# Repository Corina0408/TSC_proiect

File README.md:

link diagrama bloc: https://files.fm/u/eejnjsv4u4 

link Bill of Materials: https://docs.google.com/spreadsheets/d/1bhhom45KiLlfx5yxiHwmtoe4DynNoX60qw5_dlvZoLE/edit?usp=sharing 

Descrierea functionalitatii: 

	dispozitiv smart, construit in jurul microcontrollerului ESP32-C6, care integreaza senzori de afisaj OLED, LED RGB pentru vizual, control tactil si un potentiometru.

	Module si componente utilizate

    ESP32-C6: microcontroller principal, care gestioneaza toate componentele, comunicarea si logica dispozitivului

    BME280: senzor de temperatura, umiditate si presiune

    Display OLED (SSD1306): afiseaza informatii de la senzori si statusul sistemului

    LED RGB WS2812B: ofera feedback vizual configurabil

    TTP223: buton tactil folosit pentru interactiuni simple, cum ar fi pornirea luminii sau schimbarea modului de afisare

    Potentiometru: permite reglarea unui parametru analogic

    Reed switch: senzor magnetic digital, detecteaza apropierea unui magnet

	Interfete si comunicatie

    I2C: folosita pentru a conecta atat senzorul BME280, cat si display-ul OLED pe acelasi bus. ESP32-C6 gestioneaza ambele componente fara conflicte.

    PWM/One-wire: pentru LED-ul WS2812B, controlat prin semnal digital specific.

    Digital input: pentru butonul capacitiv si reed switch.

    Analog input (ADC): pentru citirea potentiometrului.

Procesare si comportament

ESP32-C6 colecteaza datele de la senzori si le afiseaza pe ecran. In plus, permite interactiuni tactile si vizuale cu utilizatorul

Descrierea pinilor ESP32-C6:

BME280 (I2C)

    GPIO8 (SDA) – Bus I2C partajat cu display

    GPIO9 (SCL)

OLED SSD1306 (I2C)

    GPIO8 (SDA) – Partajare eficienta de pini

    GPIO9 (SCL)

WS2812B (PWM)

    GPIO7 – Output digital cu timing precis

TTP223 (Digital)

    GPIO6 – Pin liber, ideal pentru input

Potentiometru (Analog)

    GPIO4 (ADC1) – Suporta ADC, masoara tensiune

Reed switch (Digital)

    GPIO5 – Citire stare logica simpla

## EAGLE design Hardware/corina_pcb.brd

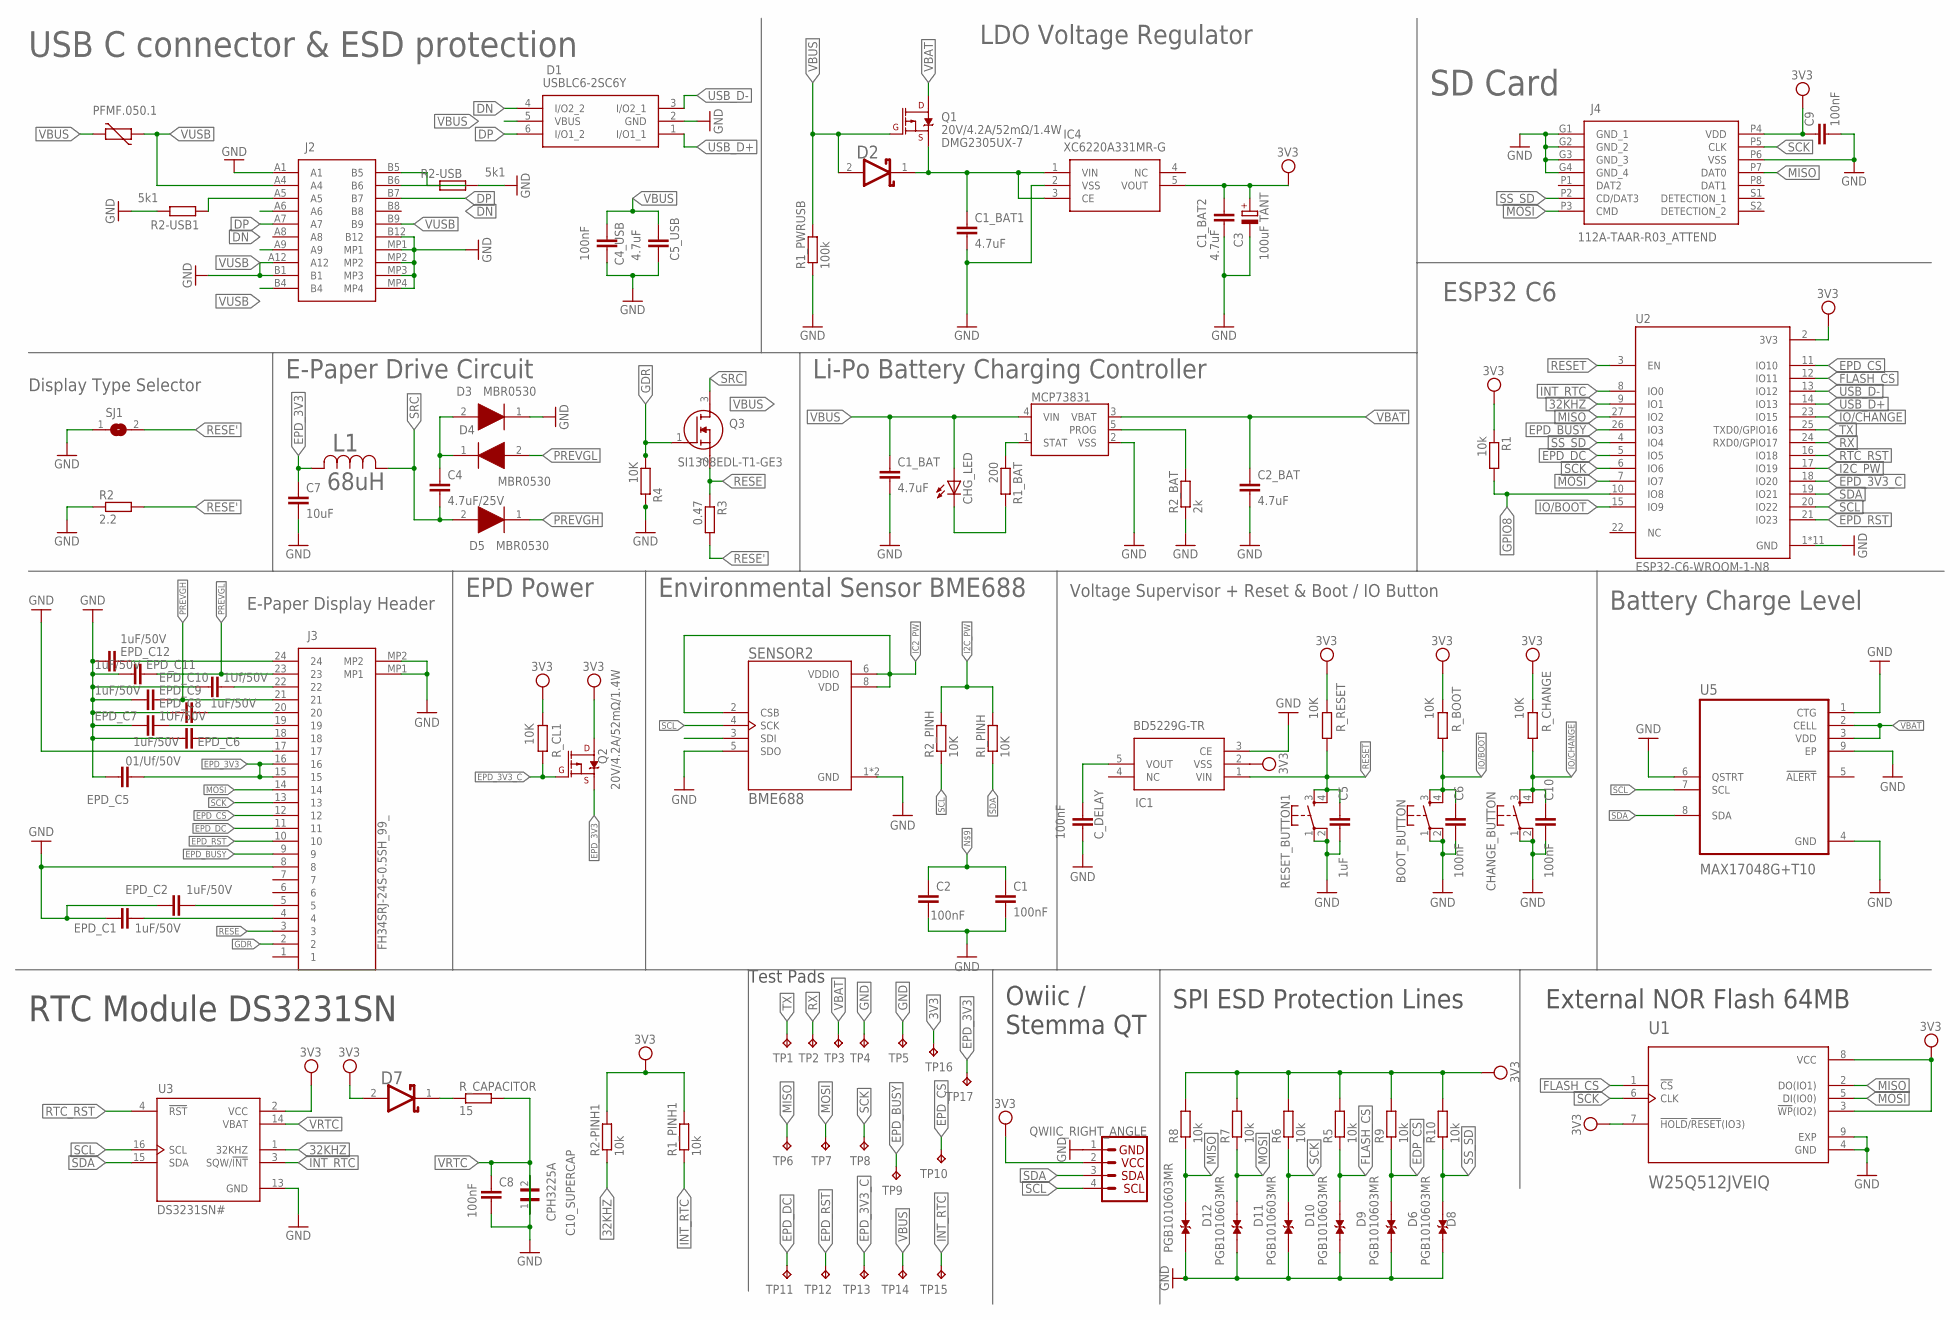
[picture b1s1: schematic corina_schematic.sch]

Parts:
BOOT_BUTTON: BUTTON_CUSYOMV1; MYBUTTON
C1, C2, C6, C8, C10: 100nF; ESP32_WROVER_EAGLE-LTSPICE_C0402
C1_BAT, C1_BAT2, C2_BAT: 4.7uF; ESP32_WROVER_EAGLE-LTSPICE_C0402
C1_BAT1, C5_USB: 4.7uF; EAGLE-LTSPICE_C0402
C3: 100uF TANT; RCL_CT3528
C4: 4.7uF/25V; ESP32_WROVER_EAGLE-LTSPICE_C0402
C4_USB, C9: 100nF; EAGLE-LTSPICE_C0402
C5: 1uF; ESP32_WROVER_EAGLE-LTSPICE_C0402
C7: 10uF; ESP32_WROVER_EAGLE-LTSPICE_C0402
C10_SUPERCAP: CPH3225A; CAPCP3225X100N
CHANGE_BUTTON: BUTTON_CUSYOMV1; MYBUTTON
CHG_LED: ADAFRUIT_LEDCHIP-LED0603; ADAFRUIT_CHIP-LED0603
C_DELAY: 100nF; ESP32_WROVER_EAGLE-LTSPICE_C0402
D1: USBLC6-2SC6Y; SOT95P280X145-6N
D2, D7: ESP32_WROVER_AVX---SD0805S020S1R0_AVX_SD0805S020S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; ESP32_WROVER_AVX---SD0805S020S1R0_AVX_SD0805S020S1R0_0
D3, D4, D5: MBR0530; SOD3716X135N
D6, D8, D9, D10, D11, D12: PGB1010603MR; DIOC1608X36N
EPD_C1, EPD_C2, EPD_C6, EPD_C8, EPD_C9, EPD_C11, EPD_C12: 1uF/50V; ESP32_WROVER_EAGLE-LTSPICE_C0402
EPD_C5: 01/Uf/50V; ESP32_WROVER_EAGLE-LTSPICE_C0402
EPD_C7: 1UF/50V; ESP32_WROVER_EAGLE-LTSPICE_C0402
EPD_C10: 1Uf/50V; ESP32_WROVER_EAGLE-LTSPICE_C0402
IC1: BD5229G-TR; SOT95P280X120-5N
IC4: XC6220A331MR-G; SOT95P280X120-5N
J1: QWIIC_RIGHT_ANGLE; JST04_1MM_RA
J2: SAMACSYS_PARTS_USB4110-GF-A; SAMACSYS_PARTS_USB4110GFA
J3: FH34SRJ-24S-0.5SH_99_; FH34SRJ24S05SH99
J4: 112A-TAAR-R03_ATTEND; 112ATAARR03ATTEND
L1: 68uH; IND_4828-WE-TPC_WRE
MCP73831: ESP32_WROVER_SPARKFUN-IC-POWER_MCP73831; ESP32_WROVER_SPARKFUN-IC-POWER_SOT23-5
PFMF.050.1: ESP32C6_VARISTORCN1812; ESP32C6_VARISTOR_CT/CN1812
Q1, Q2: 20V/4.2A/52mΩ/1.4W; ESP32_WROVER_SPARKFUN-DISCRETESEMI_SOT23-3
Q3: SI1308EDL-T1-GE3; SOT65P210X110-3N
R1, R1_PINH1, R2-PINH1, R5, R6, R7, R8, R9, R10: 10k; ESP32_WROVER_EAGLE-LTSPICE_R0402
R1_BAT: 200; ESP32_WROVER_EAGLE-LTSPICE_R0402
R1_PWRUSB: 100k; ESP32_WROVER_EAGLE-LTSPICE_R0402
R2: 2.2; ESP32_WROVER_EAGLE-LTSPICE_R0402
R2-USB, R2-USB1: 5k1; ESP32_WROVER_EAGLE-LTSPICE_R0402
R2_BAT: 2k; ESP32_WROVER_EAGLE-LTSPICE_R0402
R2_PINH, R4: 10K; ESP32_WROVER_EAGLE-LTSPICE_R0402
R3: 0.47; ESP32_WROVER_EAGLE-LTSPICE_R0402
RESET_BUTTON1: BUTTON_CUSYOMV1; MYBUTTON
RI_PINH: 10K; ESP32_WROVER_EAGLE-LTSPICE_R0402
R_BOOT: 10K; ESP32_WROVER_EAGLE-LTSPICE_R0402
R_CAPACITOR: 15; ESP32_WROVER_EAGLE-LTSPICE_R0402
R_CHANGE: 10K; ESP32_WROVER_EAGLE-LTSPICE_R0402
R_CL1: 10K; ESP32_WROVER_EAGLE-LTSPICE_R0402
R_RESET: 10K; ESP32_WROVER_EAGLE-LTSPICE_R0402
SENSOR2: BME688; ESP32_WROVER_BME680_PSON80P300X300X100-8N
SJ1: SJ
TP1, TP2, TP3, TP4, TP5, TP6, TP7, TP8, TP9, TP10, TP11, TP12, TP13, TP14, TP15, TP16, TP17: TPTP20R; TP20R
U1: W25Q512JVEIQ; SON127P600X800X80-9N
U2: ESP32-C6-WROOM-1-N8; XCVR_ESP32-C6-WROOM-1-N8
U3: DS3231SN#; SOIC127P1032X265-16N
U5: MAX17048G+T10; SON50P200X200X80-9N

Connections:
3V3: C1_BAT2.1, C3.+, C9.1, D7.2 (ANODE), IC1.2 (VSS), IC4.5 (VOUT), J1.2, J4.P4 (VDD), Q2.3 (D), R1.1, R1_PINH1.2, R2-PINH1.2, R5.2, R6.2, R7.2, R8.2, R9.2, R10.2, R_BOOT.2, R_CHANGE.2, R_CL1.2, R_RESET.2, TP16.TP, U1.3 (!WP!(IO2)), U1.7 (!HOLD!/!RESET!(IO3)), U1.8 (VCC), U2.2 (3V3), U3.2 (VCC)
32KHZ: R2-PINH1.1, U2.9 (IO1), U3.1 (32KHZ)
DN: J2.A7
DP: J2.A6
EDP_CS: D9.2, R9.1
EPD_3V3: C7.1, EPD_C5.2, J3.15, J3.16, L1.2, Q2.2 (S), TP17.TP
EPD_3V3_C: Q2.1 (G), R_CL1.1, TP13.TP, U2.18 (IO20)
EPD_BUSY: J3.9, TP9.TP, U2.26 (IO3)
EPD_CS: J3.12, TP10.TP, U2.11 (IO10)
EPD_DC: J3.11, TP11.TP, U2.5 (IO5)
EPD_RST: J3.10, TP12.TP, U2.21 (IO23)
FLASH_CS: D10.2, R5.1, U1.1 (!CS), U2.12 (IO11)
GDR: J3.2, Q3.1 (G), R4.2
GND: BOOT_BUTTON.1, BOOT_BUTTON.2, C1.2, C1_BAT.2, C1_BAT1.2, C1_BAT2.2, C2.2, C2_BAT.2, C3.-, C4_USB.2, C5.2, C5_USB.2, C6.2, C7.2, C8.2, C9.2, C10.2, C10_SUPERCAP.2, CHANGE_BUTTON.1, CHANGE_BUTTON.2, C_DELAY.2, D1.2 (GND), D3.1 (K), D6.1, D8.1, D9.1, D10.1, D11.1, D12.1, EPD_C1.1, EPD_C2.1, EPD_C5.1, EPD_C6.2, EPD_C7.2, EPD_C8.2, EPD_C9.2, EPD_C10.2, EPD_C11.2, EPD_C12.2, IC1.3 (CE), IC4.2 (VSS), J1.1, J2.A1, J2.A12, J2.B1, J2.B12, J2.MP1, J2.MP2, J2.MP3, J2.MP4, J3.8, J3.17, J3.MP1, J3.MP2, J4.G1 (GND_1), J4.G2 (GND_2), J4.G3 (GND_3), J4.G4 (GND_4), J4.P6 (VSS), MCP73831.2 (VSS), R1_PWRUSB.1, R2.1, R2-USB.2, R2-USB1.1, R2_BAT.1, R4.1, RESET_BUTTON1.1, RESET_BUTTON1.2, SENSOR2.1 (GND), SENSOR2.5 (SDO), SENSOR2.7 (GND), SJ1.1, TP4.TP, TP5.TP, U1.4 (GND), U1.9 (EXP), U2.1 (GND), U2.28 (GND), U2.29_1 (GND), U2.29_2 (GND), U2.29_3 (GND), U2.29_4 (GND), U2.29_5 (GND), U2.29_6 (GND), U2.29_7 (GND), U2.29_8 (GND), U2.29_9 (GND), U3.13 (GND), U5.1 (CTG), U5.4 (GND), U5.6 (QSTRT), U5.9 (EP)
GPIO8: R1.2, U2.10 (IO8)
I2C_PW: R2_PINH.2, RI_PINH.2, U2.17 (IO19)
IC2_PW: SENSOR2.2 (CSB), SENSOR2.6 (VDDIO), SENSOR2.8 (VDD)
INT_RTC: R1_PINH1.1, TP15.TP, U2.8 (IO0), U3.3 (SQW/!INT)
IO/BOOT: BOOT_BUTTON.3, BOOT_BUTTON.4, C6.1, R_BOOT.1, U2.15 (IO9)
IO/CHANGE: C10.1, CHANGE_BUTTON.3, CHANGE_BUTTON.4, R_CHANGE.1, U2.23 (IO15)
MISO: D8.2, J4.P7 (DAT0), R8.1, TP6.TP, U1.2 (DO(IO1))
MOSI: D12.2, J3.14, J4.P3 (CMD), R7.1, TP7.TP, U1.5 (DI(IO0))
unnamed: D7.1 (CATHODE), R_CAPACITOR.1
unnamed: J2.B5, R2-USB.1
unnamed: J2.A5, R2-USB1.2
unnamed: C1.1, C2.1
unnamed: C4_USB.1, C5_USB.1
unnamed: C1_BAT1.1, D2.1 (CATHODE), IC4.1 (VIN), IC4.3 (CE), Q1.2 (S)
unnamed: D2.2 (ANODE), Q1.1 (G), R1_PWRUSB.2
unnamed: C4.2, D5.2 (A), L1.1
unnamed: C4.1, D3.2 (A), D4.1 (K)
unnamed: MCP73831.1 (STAT), R1_BAT.1
unnamed: CHG_LED.C, R1_BAT.2
unnamed: C1_BAT.1, CHG_LED.A, MCP73831.4 (VIN)
unnamed: MCP73831.5 (PROG), R2_BAT.2
unnamed: EPD_C1.2, J3.4
unnamed: EPD_C2.2, J3.5
unnamed: EPD_C6.1, J3.18
unnamed: EPD_C7.1, J3.19
unnamed: EPD_C8.1, J3.20
unnamed: EPD_C10.1, J3.22
unnamed: EPD_C12.1, J3.24
unnamed: C_DELAY.1, IC1.5 (VOUT)
PREVGH: D5.1 (K), EPD_C9.1, J3.21
PREVGL: D4.2 (A), EPD_C11.1, J3.23
RESE: J3.3, Q3.2 (S), R3.1
RESE': SJ1.2
RESET: C5.1, IC1.1 (VIN), RESET_BUTTON1.3, RESET_BUTTON1.4, R_RESET.1, U2.3 (EN)
RTC_RST: U2.16 (IO18), U3.4 (!RST)
RX: TP2.TP, U2.24 (RXD0/GPIO17)
SCK: D11.2, J3.13, J4.P5 (CLK), R6.1, TP8.TP, U1.6 (CLK)
SCL: J1.4, R2_PINH.1, SENSOR2.4 (SCK), U2.20 (IO22), U3.16 (SCL), U5.7 (SCL)
SDA: J1.3, RI_PINH.1, SENSOR2.3 (SDI), U2.19 (IO21), U3.15 (SDA), U5.8 (SDA)
SRC: Q3.3 (D)
SS_SD: D6.2, J4.P2 (CD/DAT3), R10.1
TX: TP1.TP, U2.25 (TXD0/GPIO16)
USB_D+: D1.1 (I/O1_1)
USB_D-: D1.3 (I/O2_1)
VBAT: Q1.3 (D), TP3.TP, U5.2 (CELL), U5.3 (VDD)
VBBAT: C2_BAT.1, MCP73831.3 (VBAT)
VBUS: PFMF.050.1.2, TP14.TP
VRTC: C8.1, C10_SUPERCAP.1, R_CAPACITOR.2, U3.14 (VBAT)
VUSB: J2.A4, PFMF.050.1.1

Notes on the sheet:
RTC Module DS3231SN
Test Pads
Owiic / Stemma QT
SPI ESD Protection Lines
External NOR Flash 64MB
DMG2305UX-7
USB C connector & ESD protection
LDO Voltage Regulator
SD Card
Display Type Selector
E-Paper Drive Circuit
Li-Po Battery Charging Controller
ESP32 C6
E-Paper Display Header
EPD Power
Environmental Sensor BME688
Voltage Supervisor + Reset & Boot / IO Button
Battery Charge Level

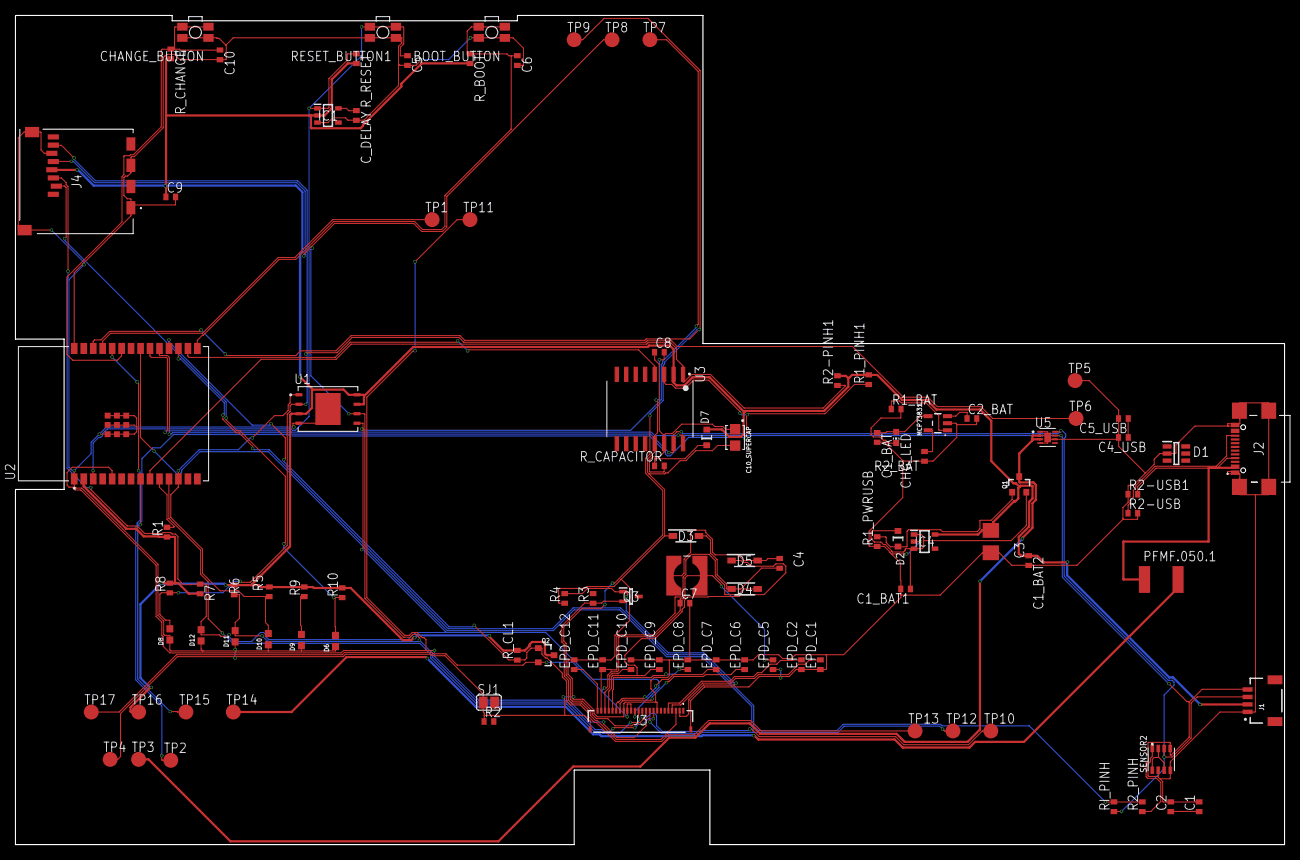
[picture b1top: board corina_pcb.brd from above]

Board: 2 copper layers, 170.2 x 111.2 mm, 103 parts (0 on the bottom side), 57 nets.

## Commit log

2025-04-06 proiect
2025-04-06 Create LICENSE

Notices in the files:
parts and their libraries:
COPYRIGHT: Copyright (C) 2024 Ultra Librarian. All rights reserved.
